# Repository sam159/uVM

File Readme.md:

# uVM

This is an 8-bit virtual machine with 16-bit addressing. It is RISC-style with no direct operations on memory, instead
operations are done on one of 16 8-bit registers with 6 16-bit registers mapped over them.

An [ASM language](ASM.md) is defined and implemented for this VM.

## Building / Running

CMake and a C build toolchain are required to build. On a debian-based system install `build-essential` and `cmake` packages.

```shell
# setup makefiles (run once)
$ cmake -DCMAKE_BUILD_TYPE=Release -G "Unix Makefiles" -S . -B ./cmake-build-release
# build project
$ cmake --build ./cmake-build-release --target uVM
```

Usage is printed with no options given.

```shell
$ ./cmake-build-release/uVM 
Usage:
  uVM program.bin                            # load at 0x0000
  uVM -a 0x100 file1.bin -a 0x200 file2.bin  # multiple files at absolute addresses
  uVM -p 0x100 program.bin                   # set PC to 0x100
  uVM -c file.asm [-o output.bin]            # assemble into binary format
```

Compiling and running asm files can be achieved with the following.  

```shell
$ ./cmake-build-release/uVM -c programs/basic.asm -o programs/basic.bin
Assembling 'programs/basic.asm' -> 'programs/basic.bin'
$ /cmake-build-release/uVM programs/basic.bin                         
Loaded 'programs/basic.bin' at 0x0000 (272 bytes)
VM Halted with code 0
PC: 0110  carry: 0  halted: 1 haltcode: 0000 (0)
R0: 00 (000) R4: 02 (002) R8: 00 (000) RC: 00 (000) 
R1: 01 (001) R5: 00 (000) R9: 00 (000) RD: 00 (000) 
R2: 64 (100) R6: 00 (000) RA: 00 (000) RE: 00 (000) 
R3: 00 (000) R7: 00 (000) RB: 00 (000) RF: 00 (000) 
RXA: 200 (00512) RXB: 00 (00000) RXE: 00 (00000)
RXC: 00 (00000) RXF: 00 (00000) RXD: 00 (00000)
```

## VM

### Registers and Flags

- **8-bit registers** 16 registers (`R0`–`RF`), 8-bit each.
- **16-bit registers** 16 registers (`RX0`-`RXF`) mapped over the 8-bit registers.
  - `RX0`-`RX9` mirroring `R0`-`RF` extended to 16-bits
  - `RXA`-`RXF` mapped to pairs of 8-bit registers
- **R0/RX0** always reads as 0. Writes to R0 are a no-op.
- **PC** (program counter), 16-bit. Increments by 2 each instruction fetch. Must be word-aligned.
- **carry**, 1-bit flag used by ADC and SBC.

### 16-bit Register Mapping

Some instructions can use two 8-bit registers as one 16-bit register for addressing. 

The upper 12 registers form six extended 16-bit address registers (big-endian, high byte : low byte):

| Alias | Registers |
|-------|-----------|
| RXA   | R4 : R5   |
| RXB   | R6 : R7   |
| RXC   | R8 : R9   |
| RXD   | RA : RB   |
| RXE   | RC : RD   |
| RXF   | RE : RF   |

`vm_get_rx()` returns the 16-bit value of a register: 0x0-0x9 return the 8-bit variant, with 0xA-0xF returning the above registers.  

### Memory

- 64KB address space (0x0000 - 0xFFFF).
- All operations work on registers only, no direct memory-to-memory operations.
- Memory access is via hook functions: `readAddr` and `writeAddr` on the VM struct.

### Instruction Format

All instructions are two bytes (big-endian). The upper four bits are the opcode. Three operand formats share the lower 12 bits:

| Format | Layout (16 bits)             | Description                                     |
|--------|------------------------------|-------------------------------------------------|
| Q      | `[op:4][rd:4][imm8:8]`       | Destination register + 8-bit immediate          |
| S      | `[op:4][rd:4][rx:4][ry:4]`   | Destination + two source registers              |
| T      | `[op:4][rd:4][rx:4][imm4:4]` | Destination + source register + 4-bit immediate |
| V      | `[op:4][imm12:12]`           | 12-bit immediate                                |

## Operations / Opcodes

Operand terms
- `exitcode` - sets the vm exitcode
- `rd`/`rx`/`ry` - 8-bit register
- `rdx` - `rd` with extended register support
- `imm4` - immediate value 4-bit
- `imm4_s` - immediate value 4-bit
- `imm4_s_x2` - immediate value 4-bit multiplied by two
- `test` - a conditional jump type
- `imm8` - immediate value 8-bit 
- `imm8_s` - signed immediate value 8-bit 
- `imm8_s_x2` - signed immediate value 8-bit multiplied by two
- `imm12` - immediate value 12-bit
- `imm12_s` - signed immediate value 12-bit
- `imm12_s_x2` - signed immediate value 12-bit multiplied by two
- `carry` - carry flag

All jumps are in words/instructions. 

| Op  | Mnemonic | Format | Operation                          | Description                                                                               |
|-----|----------|--------|------------------------------------|-------------------------------------------------------------------------------------------------|
| `0` | HLT      | Q      | `exitcode ← rd + imm8`                 | Halt the VM. Sets `halted = true`, and the exit code to `rd` + `imm8`                           |
| `1` | LDA      | T      | `rd ← [rdx + imm4]`                | Load byte from memory at 16-bit address `rdx + imm4` into `rd`                            |
| `2` | STA      | T      | `[rdx + imm4] ← rx`                | Store `rx` to memory at 16-bit address `rdx + imm4`                                       |
| `3` | LDI      | Q      | `rd ← imm8`                        | Load `imm8` into `rd`                                                                     |
| `4` | ADD      | S      | `rd ← rx + ry`                     | 8-bit add. Sets carry on overflow                                                                   |
| `5` | ADC      | S      | `rd ← rx + ry + carry`             | 8-bit add with carry. Sets carry on overflow                                              |
| `6` | SUB      | S      | `rd ← rx - ry`                     | 8-bit subtract. Clears carry                                                              |
| `7` | SBC      | S      | `rd ← rx - ry - carry`             | 8-bit subtract with borrow. Propagates borrow bit-by-bit into carry                       |
| `8` | NOT      | T      | `rd ← ~rx`                         | Bitwise NOT of `rx`                                                                       |
| `9` | BIT      | T      | `rd ← rd OP rx`                    | Bitwise operation on `rd` using `rx`. OP: 0=AND, 1=OR, 2=XOR, 4=MOD                       |
| `A` | SHL      | T      | `rd ← rx << imm4`                  | Logical left shift by `imm` bits                                                          |
| `B` | SHR      | T      | `rd ← rx >> imm4`                  | Logical right shift by `imm` bits                                                         |
| `C` | JMP      | V      | `PC ← PC + imm12_s_x2`             | Relative jump. Update PC with `imm12_s_x2`                                                |
| `D` | JPF      | Q      | `PC ← rdx + imm8_s_x2`             | Far jump. Set PC to the value in `rdx` with `imm8_s_x2` value                             |
| `E` | JNZ      | Q      | `PC ← PC + imm8_s_x2` if `rd != 0` | Conditional jump. Add `imm8_s_x2` to PC if `rd` is not zero                               |
| `F` | JPC      | T      | `PC ← PC + 2` if `!test(rd,rx)`    | Conditional jump. Skips the next instruction if `test` passes for values in `rd` and `rx` |

### Conditional Jumps

Test types, used for comparing values in `rd` and `rx`.

Tests are mapped into a 4-bit value and can be in any combination
```text
3   2   1   0
|   |   |   |
|   |   |   +-- Equality
|   |   +------ Less Than
|   +---------- Greater Than
+-------------- Negate Result
```

Setting bits 0–3 will pass for any value, negating it will not pass for any value,
similarly not setting any bits will not pass for any value.

| Mnemonic | Number | Binary | Test                                         |
|----------|--------|--------|----------------------------------------------|
| EQ       | 1      | 0001   | Equals                                       |
| ~EQ      | 9      | 1001   | Not equals                                   |
| LT       | 2      | 0010   | Less than                                    |
| ~LT      | 10     | 1010   | Not less than                                |
| LTE      | 3      | 0011   | Less than or equal                           |
| ~LTE     | 11     | 1011   | Not less than or equal                       |
| GT       | 4      | 0100   | Greater than                                 |
| ~GT      | 12     | 1100   | Not greater than                             |
| GTE      | 5      | 0101   | Greater than or equal                        |
| ~GTE     | 13     | 1101   | Not greater than or equal                    |

## Error Handling

Errors are reported via the `error` hook and halt the VM:

| Code | Constant               | Condition                                                           |
|------|------------------------|---------------------------------------------------------------------|
| 1    | `VM_ERR_MISALIGN`      | PC is not word-aligned on instruction fetch.                        |
| 2    | `VM_ERR_UNKNOWN_OP`    | Opcode is not recognized (0–F). Redundant, exists for completeness. |
| 3    | `VM_ERR_OUT_OF_BOUNDS` | Memory access address >= 0x10000.                                   |
| 4    | `VM_ERR_JUMP_SELF`     | An jump instruction jumped to itself                                |
| 5    | `VM_ERR_INVALID_BIT_OP`| BIT instruction has invalid operation code (not 0, 1, 2, or 4).     |

## Execution Model

1. `vm_step()` fetches one 2-byte instruction from `readAddr(PC)`.
2. Decodes the opcode and operand format.
3. Executes the operation, writing the result to `rd` via `vm_put_r()`.
4. Increments PC by 2 (except for jumps which set PC directly).
5. The main loop calls `vm_step()` repeatedly until `vm->halted` is true.

## TODO

ASM
- allow variables in STA/LDA address offset
- allow referencing variable high/low byte with `:h`/`:l`

VM
- Add device support
  - File

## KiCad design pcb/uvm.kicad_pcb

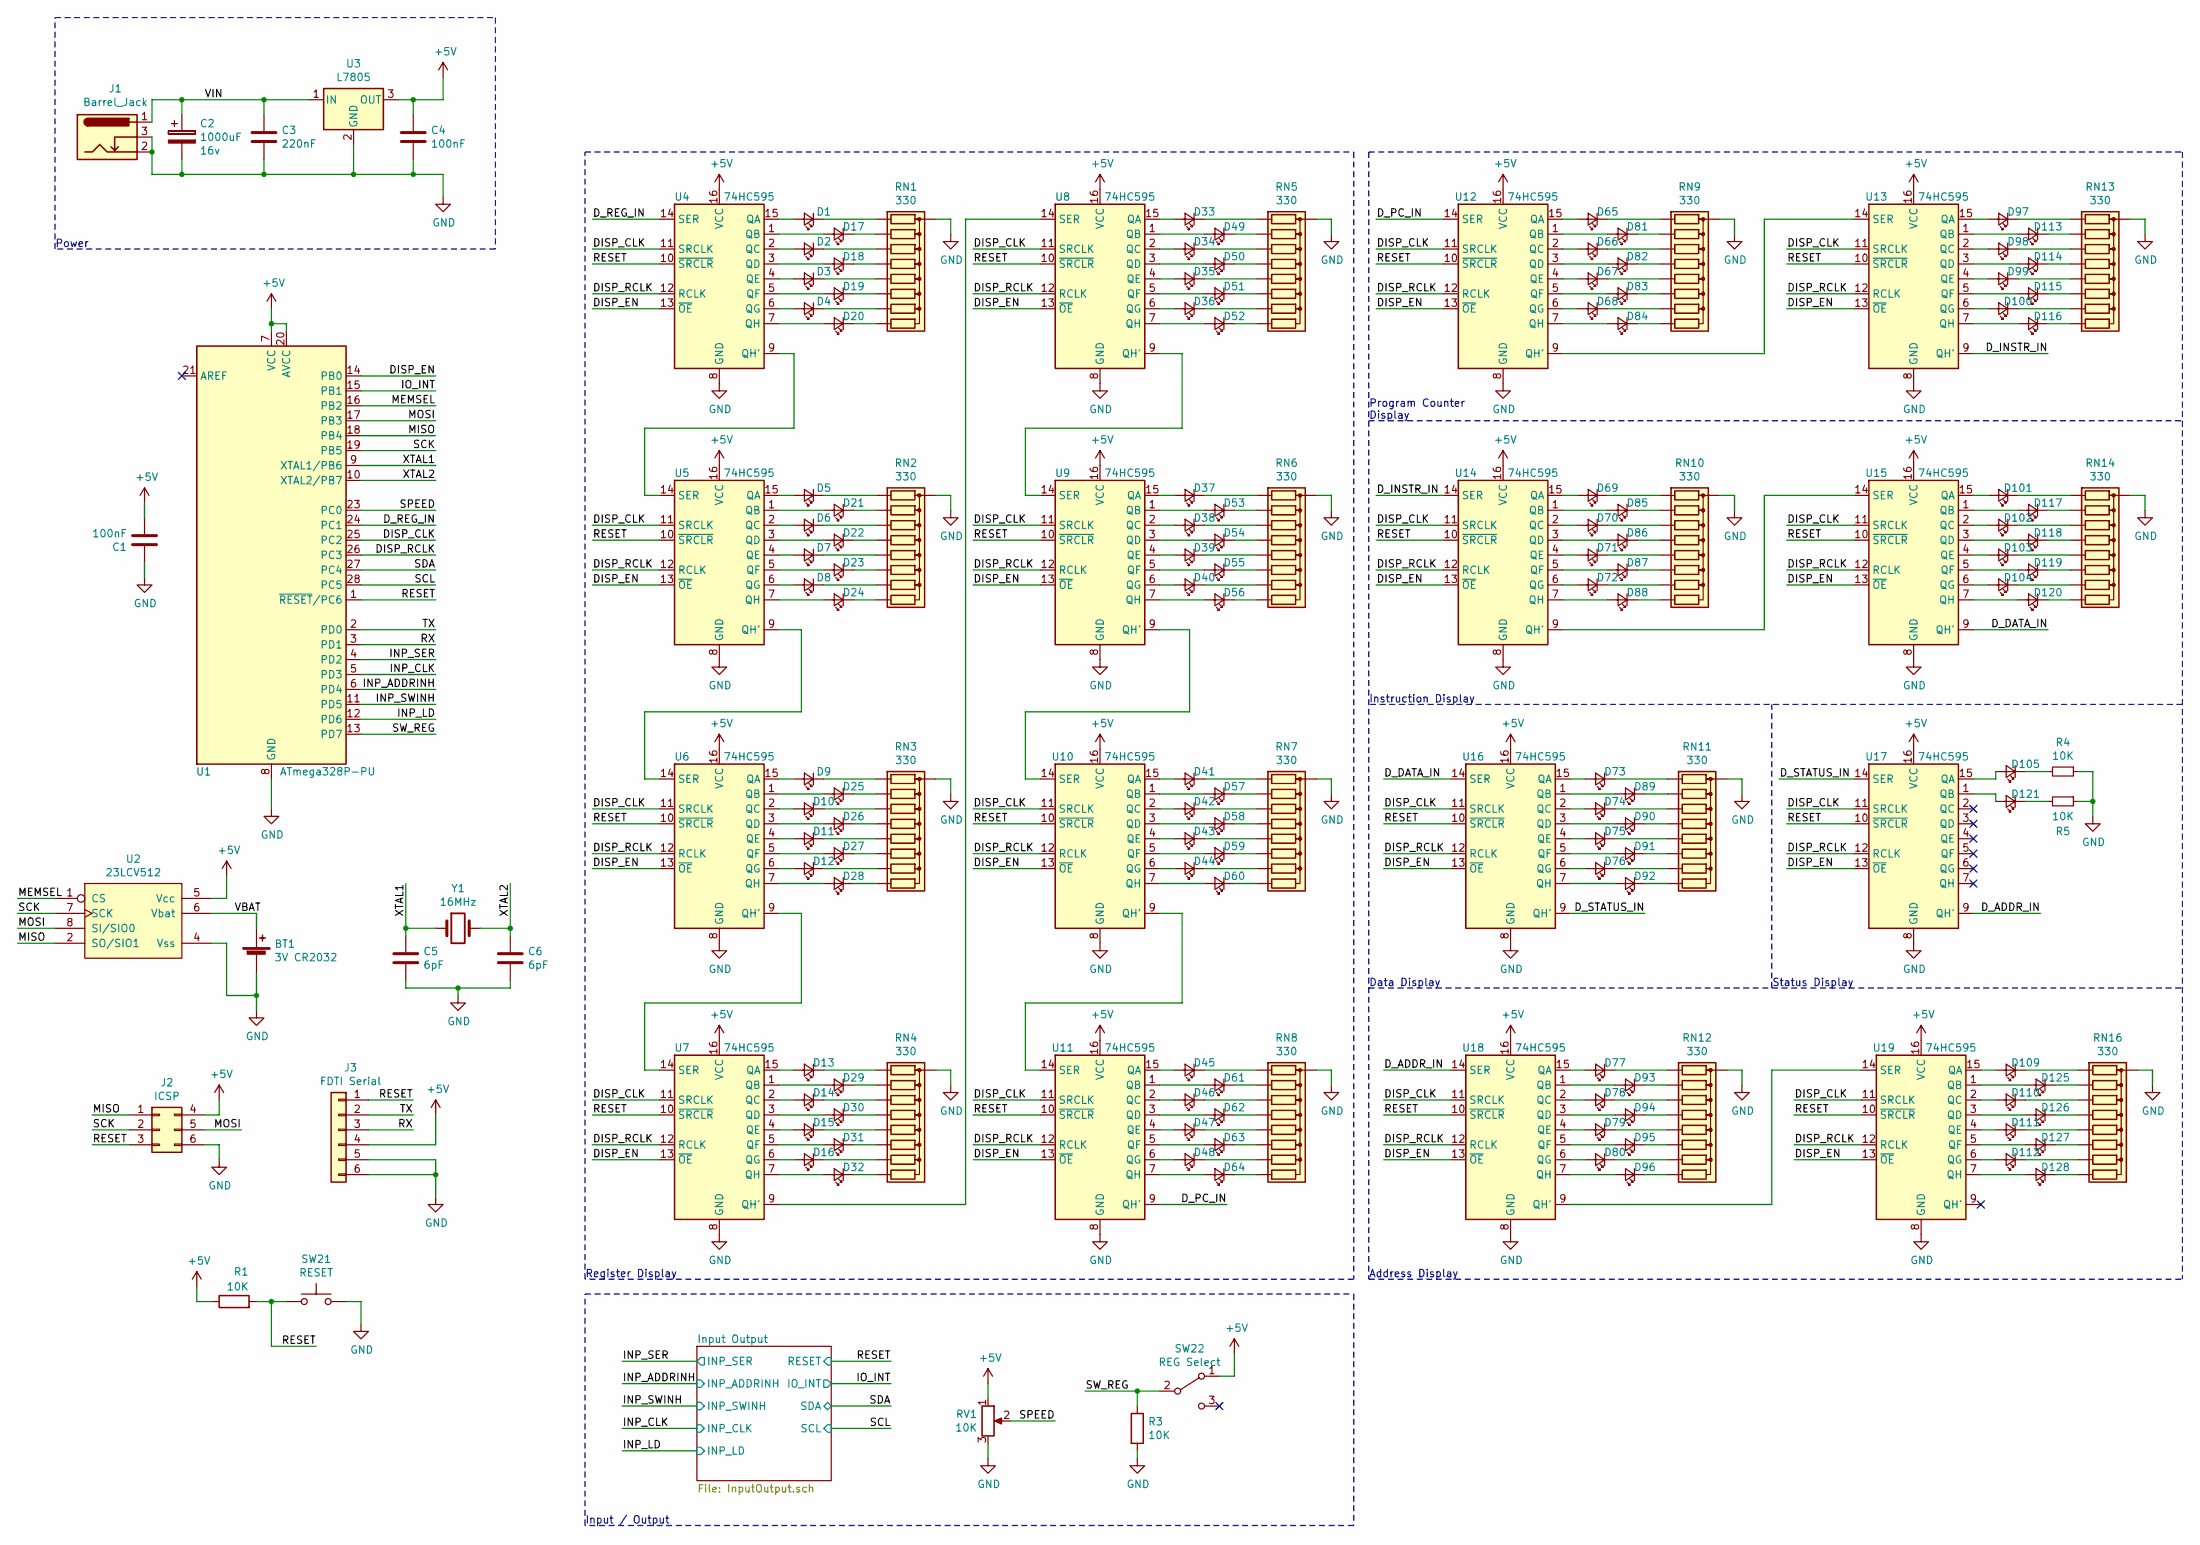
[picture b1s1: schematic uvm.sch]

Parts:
BT1: 3V CR2032; BatteryHolder_Keystone_105_1x2430
C1, C4: 100nF; C_Disc_D6.0mm_W2.5mm_P5.00mm
C2: 1000uF; CP_Radial_D8.0mm_P3.80mm; Rating 16v
C3: 220nF; C_Disc_D4.7mm_W2.5mm_P5.00mm
C5, C6: 6pF; C_Disc_D6.0mm_W2.5mm_P5.00mm
D1, D2, D3, D4, D5, D6, D7, D8, D9, D10, D11, D12, D13, D14, D15, D16, D17, D18, D19, D20, D21, D22, D23, D24, D25, D26, D27, D28, D29, D30, D31, D32, D33, D34, D35, D36, D37, D38, D39, D40, D41, D42, D43, D44, D45, D46, D47, D48, D49, D50, D51, D52, D53, D54, D55, D56, D57, D58, D59, D60, D61, D62, D63, D64, D65, D66, D67, D68, D69, D70, D71, D72, D73, D74, D75, D76, D77, D78, D79, D80, D81, D82, D83, D84, D85, D86, D87, D88, D89, D90, D91, D92, D93, D94, D95, D96, D97, D98, D99, D100, D101, D102, D103, D104, D105, D109, D110, D111, D112, D113, D114, D115, D116, D117, D118, D119, D120, D121, D125, D126, D127, D128: LED; LED_D5.0mm
J1: Barrel_Jack; BarrelJack_Horizontal
J2: ICSP; PinHeader_2x03_P2.54mm_Vertical
J3: FDTI Serial; PinHeader_1x06_P2.54mm_Vertical
R1, R3, R4, R5: 10K; R_Axial_DIN0207_L6.3mm_D2.5mm_P10.16mm_Horizontal
RN1, RN2, RN3, RN4, RN5, RN6, RN7, RN8, RN9, RN10, RN11, RN12, RN13, RN14, RN16: 330; R_Array_SIP9
RV1: 10K; Potentiometer_Alps_RK09K_Single_Vertical
SW21: RESET; SW_PUSH_6mm_H5mm
SW22: REG Select; TOGGLE_SPDT_ON_ON_2MS
U1: ATmega328P-PU; DIP-28_W7.62mm_Socket
U2: 23LCV512; DIP-8_W7.62mm_Socket
U3: L7805; TO-220-3_Horizontal_TabDown
U4, U5, U6, U7, U8, U9, U10, U11, U12, U13, U14, U15, U16, U17, U18, U19: 74HC595; DIP-16_W7.62mm
Y1: 16MHz; Crystal_HC18-U_Vertical

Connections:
+5V: C1.2, C4.1, J2.4, J3.4, R1.1, RV1.1, SW22.1 (A), U1.7 (VCC), U1.20 (AVCC), U2.5 (Vcc), U3.3 (OUT), U4.16 (VCC), U5.16 (VCC), U6.16 (VCC), U7.16 (VCC), U8.16 (VCC), U9.16 (VCC), U10.16 (VCC), U11.16 (VCC), U12.16 (VCC), U13.16 (VCC), U14.16 (VCC), U15.16 (VCC), U16.16 (VCC), U17.16 (VCC), U18.16 (VCC), U19.16 (VCC); also elsewhere on the board
/DISP_CLK: U1.25 (PC2), U4.11 (SRCLK), U5.11 (SRCLK), U6.11 (SRCLK), U7.11 (SRCLK), U8.11 (SRCLK), U9.11 (SRCLK), U10.11 (SRCLK), U11.11 (SRCLK), U12.11 (SRCLK), U13.11 (SRCLK), U14.11 (SRCLK), U15.11 (SRCLK), U16.11 (SRCLK), U17.11 (SRCLK), U18.11 (SRCLK), U19.11 (SRCLK)
/DISP_EN: U1.14 (PB0), U4.13 (~OE), U5.13 (~OE), U6.13 (~OE), U7.13 (~OE), U8.13 (~OE), U9.13 (~OE), U10.13 (~OE), U11.13 (~OE), U12.13 (~OE), U13.13 (~OE), U14.13 (~OE), U15.13 (~OE), U16.13 (~OE), U17.13 (~OE), U18.13 (~OE), U19.13 (~OE)
/DISP_RCLK: U1.26 (PC3), U4.12 (RCLK), U5.12 (RCLK), U6.12 (RCLK), U7.12 (RCLK), U8.12 (RCLK), U9.12 (RCLK), U10.12 (RCLK), U11.12 (RCLK), U12.12 (RCLK), U13.12 (RCLK), U14.12 (RCLK), U15.12 (RCLK), U16.12 (RCLK), U17.12 (RCLK), U18.12 (RCLK), U19.12 (RCLK)
/D_ADDR_IN: U17.9 (QH'), U18.14 (SER)
/D_DATA_IN: U15.9 (QH'), U16.14 (SER)
/D_INSTR_IN: U13.9 (QH'), U14.14 (SER)
/D_PC_IN: U11.9 (QH'), U12.14 (SER)
/D_REG_IN: U1.24 (PC1), U4.14 (SER)
/D_STATUS_IN: U16.9 (QH'), U17.14 (SER)
/INP_ADDRINH: U1.6 (PD4); also elsewhere on the board
/INP_CLK: U1.5 (PD3); also elsewhere on the board
/INP_LD: U1.12 (PD6); also elsewhere on the board
/INP_SER: U1.4 (PD2); also elsewhere on the board
/INP_SWINH: U1.11 (PD5); also elsewhere on the board
/IO_INT: U1.15 (PB1); also elsewhere on the board
/MEMSEL: U1.16 (PB2), U2.1 (CS)
/MISO: J2.1, U1.18 (PB4), U2.2 (SO/SIO1)
/MOSI: J2.5, U1.17 (PB3), U2.8 (SI/SIO0)
/RESET: J2.3, J3.1, R1.2, SW21.1, U1.1 (~RESET~/PC6), U4.10 (~SRCLR), U5.10 (~SRCLR), U6.10 (~SRCLR), U7.10 (~SRCLR), U8.10 (~SRCLR), U9.10 (~SRCLR), U10.10 (~SRCLR), U11.10 (~SRCLR), U12.10 (~SRCLR), U13.10 (~SRCLR), U14.10 (~SRCLR), U15.10 (~SRCLR), U16.10 (~SRCLR), U17.10 (~SRCLR), U18.10 (~SRCLR), U19.10 (~SRCLR); also elsewhere on the board
/RX: J3.3, U1.3 (PD1)
/SCK: J2.2, U1.19 (PB5), U2.7 (SCK)
/SCL: U1.28 (PC5); also elsewhere on the board
/SDA: U1.27 (PC4); also elsewhere on the board
/SPEED: RV1.2, U1.23 (PC0)
/SW_REG: R3.1, SW22.2 (B), U1.13 (PD7)
/TX: J3.2, U1.2 (PD0)
/VBAT: BT1.1 (+), U2.6 (Vbat)
/VIN: C2.1, C3.1, J1.1, U3.1 (IN)
/XTAL1: C5.1, U1.9 (XTAL1/PB6), Y1.1
/XTAL2: C6.1, U1.10 (XTAL2/PB7), Y1.2
GND: BT1.2 (-), C1.1, C2.2, C3.2, C4.2, C5.2, C6.2, J1.2, J1.3, J2.6, J3.5, J3.6, R3.2, R4.1, R5.1, RN1.1 (common), RN2.1 (common), RN3.1 (common), RN4.1 (common), RN5.1 (common), RN6.1 (common), RN7.1 (common), RN8.1 (common), RN9.1 (common), RN10.1 (common), RN11.1 (common), RN12.1 (common), RN13.1 (common), RN14.1 (common), RN16.1 (common), RV1.3, SW21.2, U1.8 (GND), U1.22 (GND), U2.4 (Vss), U3.2 (GND), U4.8 (GND), U5.8 (GND), U6.8 (GND), U7.8 (GND), U8.8 (GND), U9.8 (GND), U10.8 (GND), U11.8 (GND), U12.8 (GND), U13.8 (GND), U14.8 (GND), U15.8 (GND), U16.8 (GND), U17.8 (GND), U18.8 (GND), U19.8 (GND); also elsewhere on the board
unnamed: D1.1 (K), RN1.2 (R1)
unnamed: D1.2 (A), U4.15 (QA)
unnamed: D2.1 (K), RN1.4 (R3)
unnamed: D2.2 (A), U4.2 (QC)
unnamed: D3.1 (K), RN1.6 (R5)
unnamed: D3.2 (A), U4.4 (QE)
unnamed: D4.1 (K), RN1.8 (R7)
unnamed: D4.2 (A), U4.6 (QG)
unnamed: D5.1 (K), RN2.2 (R1)
unnamed: D5.2 (A), U5.15 (QA)
unnamed: D6.1 (K), RN2.4 (R3)
unnamed: D6.2 (A), U5.2 (QC)
unnamed: D7.1 (K), RN2.6 (R5)
unnamed: D7.2 (A), U5.4 (QE)
unnamed: D8.1 (K), RN2.8 (R7)
unnamed: D8.2 (A), U5.6 (QG)
unnamed: D9.1 (K), RN3.2 (R1)
unnamed: D9.2 (A), U6.15 (QA)
unnamed: D10.1 (K), RN3.4 (R3)
unnamed: D10.2 (A), U6.2 (QC)
unnamed: D11.1 (K), RN3.6 (R5)
unnamed: D11.2 (A), U6.4 (QE)
unnamed: D12.1 (K), RN3.8 (R7)
unnamed: D12.2 (A), U6.6 (QG)
unnamed: D13.1 (K), RN4.2 (R1)
unnamed: D13.2 (A), U7.15 (QA)
unnamed: D14.1 (K), RN4.4 (R3)
unnamed: D14.2 (A), U7.2 (QC)
unnamed: D15.1 (K), RN4.6 (R5)
unnamed: D15.2 (A), U7.4 (QE)
unnamed: D16.1 (K), RN4.8 (R7)
unnamed: D16.2 (A), U7.6 (QG)
unnamed: D17.1 (K), RN1.3 (R2)
unnamed: D17.2 (A), U4.1 (QB)
unnamed: D18.1 (K), RN1.5 (R4)
unnamed: D18.2 (A), U4.3 (QD)
unnamed: D19.1 (K), RN1.7 (R6)
unnamed: D19.2 (A), U4.5 (QF)
unnamed: D20.1 (K), RN1.9 (R8)
unnamed: D20.2 (A), U4.7 (QH)
unnamed: D21.1 (K), RN2.3 (R2)
unnamed: D21.2 (A), U5.1 (QB)
unnamed: D22.1 (K), RN2.5 (R4)
unnamed: D22.2 (A), U5.3 (QD)
unnamed: D23.1 (K), RN2.7 (R6)
unnamed: D23.2 (A), U5.5 (QF)
unnamed: D24.1 (K), RN2.9 (R8)
unnamed: D24.2 (A), U5.7 (QH)
unnamed: D25.1 (K), RN3.3 (R2)
unnamed: D25.2 (A), U6.1 (QB)
unnamed: D26.1 (K), RN3.5 (R4)
unnamed: D26.2 (A), U6.3 (QD)
unnamed: D27.1 (K), RN3.7 (R6)
unnamed: D27.2 (A), U6.5 (QF)
unnamed: D28.1 (K), RN3.9 (R8)
unnamed: D28.2 (A), U6.7 (QH)
unnamed: D29.1 (K), RN4.3 (R2)
unnamed: D29.2 (A), U7.1 (QB)
unnamed: D30.1 (K), RN4.5 (R4)
unnamed: D30.2 (A), U7.3 (QD)
unnamed: D31.1 (K), RN4.7 (R6)
unnamed: D31.2 (A), U7.5 (QF)
unnamed: D32.1 (K), RN4.9 (R8)
unnamed: D32.2 (A), U7.7 (QH)
unnamed: D33.1 (K), RN5.2 (R1)
unnamed: D33.2 (A), U8.15 (QA)
unnamed: D34.1 (K), RN5.4 (R3)
unnamed: D34.2 (A), U8.2 (QC)
unnamed: D35.1 (K), RN5.6 (R5)
unnamed: D35.2 (A), U8.4 (QE)
unnamed: D36.1 (K), RN5.8 (R7)
unnamed: D36.2 (A), U8.6 (QG)
unnamed: D37.1 (K), RN6.2 (R1)
unnamed: D37.2 (A), U9.15 (QA)
unnamed: D38.1 (K), RN6.4 (R3)
unnamed: D38.2 (A), U9.2 (QC)
unnamed: D39.1 (K), RN6.6 (R5)
unnamed: D39.2 (A), U9.4 (QE)
unnamed: D40.1 (K), RN6.8 (R7)
unnamed: D40.2 (A), U9.6 (QG)
unnamed: D41.1 (K), RN7.2 (R1)
unnamed: D41.2 (A), U10.15 (QA)
unnamed: D42.1 (K), RN7.4 (R3)
unnamed: D42.2 (A), U10.2 (QC)
unnamed: D43.1 (K), RN7.6 (R5)
unnamed: D43.2 (A), U10.4 (QE)
unnamed: D44.1 (K), RN7.8 (R7)
unnamed: D44.2 (A), U10.6 (QG)
unnamed: D45.1 (K), RN8.2 (R1)
unnamed: D45.2 (A), U11.15 (QA)
unnamed: D46.1 (K), RN8.4 (R3)
unnamed: D46.2 (A), U11.2 (QC)
unnamed: D47.1 (K), RN8.6 (R5)
unnamed: D47.2 (A), U11.4 (QE)
unnamed: D48.1 (K), RN8.8 (R7)
unnamed: D48.2 (A), U11.6 (QG)
unnamed: D49.1 (K), RN5.3 (R2)
unnamed: D49.2 (A), U8.1 (QB)
unnamed: D50.1 (K), RN5.5 (R4)
unnamed: D50.2 (A), U8.3 (QD)
unnamed: D51.1 (K), RN5.7 (R6)
unnamed: D51.2 (A), U8.5 (QF)
unnamed: D52.1 (K), RN5.9 (R8)
unnamed: D52.2 (A), U8.7 (QH)
unnamed: D53.1 (K), RN6.3 (R2)
unnamed: D53.2 (A), U9.1 (QB)
unnamed: D54.1 (K), RN6.5 (R4)
unnamed: D54.2 (A), U9.3 (QD)
unnamed: D55.1 (K), RN6.7 (R6)
unnamed: D55.2 (A), U9.5 (QF)
unnamed: D56.1 (K), RN6.9 (R8)
unnamed: D56.2 (A), U9.7 (QH)
unnamed: D57.1 (K), RN7.3 (R2)
unnamed: D57.2 (A), U10.1 (QB)
unnamed: D58.1 (K), RN7.5 (R4)
unnamed: D58.2 (A), U10.3 (QD)
unnamed: D59.1 (K), RN7.7 (R6)
unnamed: D59.2 (A), U10.5 (QF)
unnamed: D60.1 (K), RN7.9 (R8)
unnamed: D60.2 (A), U10.7 (QH)
unnamed: D61.1 (K), RN8.3 (R2)
unnamed: D61.2 (A), U11.1 (QB)
unnamed: D62.1 (K), RN8.5 (R4)
unnamed: D62.2 (A), U11.3 (QD)
unnamed: D63.1 (K), RN8.7 (R6)
unnamed: D63.2 (A), U11.5 (QF)
unnamed: D64.1 (K), RN8.9 (R8)
unnamed: D64.2 (A), U11.7 (QH)
unnamed: D65.1 (K), RN9.2 (R1)
unnamed: D65.2 (A), U12.15 (QA)
unnamed: D66.1 (K), RN9.4 (R3)
unnamed: D66.2 (A), U12.2 (QC)
unnamed: D67.1 (K), RN9.6 (R5)
unnamed: D67.2 (A), U12.4 (QE)
unnamed: D68.1 (K), RN9.8 (R7)
unnamed: D68.2 (A), U12.6 (QG)
unnamed: D69.1 (K), RN10.2 (R1)
unnamed: D69.2 (A), U14.15 (QA)
unnamed: D70.1 (K), RN10.4 (R3)
unnamed: D70.2 (A), U14.2 (QC)
unnamed: D71.1 (K), RN10.6 (R5)
unnamed: D71.2 (A), U14.4 (QE)
unnamed: D72.1 (K), RN10.8 (R7)
unnamed: D72.2 (A), U14.6 (QG)
unnamed: D73.1 (K), RN11.2 (R1)
unnamed: D73.2 (A), U16.15 (QA)
unnamed: D74.1 (K), RN11.4 (R3)
unnamed: D74.2 (A), U16.2 (QC)
unnamed: D75.1 (K), RN11.6 (R5)
unnamed: D75.2 (A), U16.4 (QE)
unnamed: D76.1 (K), RN11.8 (R7)
unnamed: D76.2 (A), U16.6 (QG)
unnamed: D77.1 (K), RN12.2 (R1)
unnamed: D77.2 (A), U18.15 (QA)
unnamed: D78.1 (K), RN12.4 (R3)
unnamed: D78.2 (A), U18.2 (QC)
unnamed: D79.1 (K), RN12.6 (R5)
unnamed: D79.2 (A), U18.4 (QE)
unnamed: D80.1 (K), RN12.8 (R7)
unnamed: D80.2 (A), U18.6 (QG)
unnamed: D81.1 (K), RN9.3 (R2)
unnamed: D81.2 (A), U12.1 (QB)
unnamed: D82.1 (K), RN9.5 (R4)
unnamed: D82.2 (A), U12.3 (QD)
unnamed: D83.1 (K), RN9.7 (R6)
unnamed: D83.2 (A), U12.5 (QF)
unnamed: D84.1 (K), RN9.9 (R8)
unnamed: D84.2 (A), U12.7 (QH)
unnamed: D85.1 (K), RN10.3 (R2)
unnamed: D85.2 (A), U14.1 (QB)
unnamed: D86.1 (K), RN10.5 (R4)
unnamed: D86.2 (A), U14.3 (QD)
unnamed: D87.1 (K), RN10.7 (R6)
unnamed: D87.2 (A), U14.5 (QF)
unnamed: D88.1 (K), RN10.9 (R8)
unnamed: D88.2 (A), U14.7 (QH)
unnamed: D89.1 (K), RN11.3 (R2)
unnamed: D89.2 (A), U16.1 (QB)
unnamed: D90.1 (K), RN11.5 (R4)
unnamed: D90.2 (A), U16.3 (QD)
unnamed: D91.1 (K), RN11.7 (R6)
unnamed: D91.2 (A), U16.5 (QF)
unnamed: D92.1 (K), RN11.9 (R8)
unnamed: D92.2 (A), U16.7 (QH)
unnamed: D93.1 (K), RN12.3 (R2)
unnamed: D93.2 (A), U18.1 (QB)
unnamed: D94.1 (K), RN12.5 (R4)
unnamed: D94.2 (A), U18.3 (QD)
unnamed: D95.1 (K), RN12.7 (R6)
unnamed: D95.2 (A), U18.5 (QF)
unnamed: D96.1 (K), RN12.9 (R8)
unnamed: D96.2 (A), U18.7 (QH)
unnamed: D97.1 (K), RN13.2 (R1)
unnamed: D97.2 (A), U13.15 (QA)
unnamed: D98.1 (K), RN13.4 (R3)
unnamed: D98.2 (A), U13.2 (QC)
unnamed: D99.1 (K), RN13.6 (R5)
unnamed: D99.2 (A), U13.4 (QE)
unnamed: D100.1 (K), RN13.8 (R7)
unnamed: D100.2 (A), U13.6 (QG)
unnamed: D101.1 (K), RN14.2 (R1)
unnamed: D101.2 (A), U15.15 (QA)
unnamed: D102.1 (K), RN14.4 (R3)
unnamed: D102.2 (A), U15.2 (QC)
unnamed: D103.1 (K), RN14.6 (R5)
unnamed: D103.2 (A), U15.4 (QE)
unnamed: D104.1 (K), RN14.8 (R7)
unnamed: D104.2 (A), U15.6 (QG)
unnamed: D105.1 (K), R4.2
unnamed: D105.2 (A), U17.15 (QA)
unnamed: D109.1 (K), RN16.2 (R1)
unnamed: D109.2 (A), U19.15 (QA)
unnamed: D110.1 (K), RN16.4 (R3)
unnamed: D110.2 (A), U19.2 (QC)
unnamed: D111.1 (K), RN16.6 (R5)
unnamed: D111.2 (A), U19.4 (QE)
unnamed: D112.1 (K), RN16.8 (R7)
unnamed: D112.2 (A), U19.6 (QG)
unnamed: D113.1 (K), RN13.3 (R2)
unnamed: D113.2 (A), U13.1 (QB)
unnamed: D114.1 (K), RN13.5 (R4)
unnamed: D114.2 (A), U13.3 (QD)
unnamed: D115.1 (K), RN13.7 (R6)
unnamed: D115.2 (A), U13.5 (QF)
unnamed: D116.1 (K), RN13.9 (R8)
unnamed: D116.2 (A), U13.7 (QH)
unnamed: D117.1 (K), RN14.3 (R2)
unnamed: D117.2 (A), U15.1 (QB)
unnamed: D118.1 (K), RN14.5 (R4)
unnamed: D118.2 (A), U15.3 (QD)
unnamed: D119.1 (K), RN14.7 (R6)
unnamed: D119.2 (A), U15.5 (QF)
unnamed: D120.1 (K), RN14.9 (R8)
unnamed: D120.2 (A), U15.7 (QH)
unnamed: D121.1 (K), R5.2
unnamed: D121.2 (A), U17.1 (QB)
unnamed: D125.1 (K), RN16.3 (R2)
unnamed: D125.2 (A), U19.1 (QB)
unnamed: D126.1 (K), RN16.5 (R4)
unnamed: D126.2 (A), U19.3 (QD)
unnamed: D127.1 (K), RN16.7 (R6)
unnamed: D127.2 (A), U19.5 (QF)
unnamed: D128.1 (K), RN16.9 (R8)
unnamed: D128.2 (A), U19.7 (QH)
unnamed: U4.9 (QH'), U5.14 (SER)
unnamed: U5.9 (QH'), U6.14 (SER)
unnamed: U6.9 (QH'), U7.14 (SER)
unnamed: U7.9 (QH'), U8.14 (SER)
unnamed: U8.9 (QH'), U9.14 (SER)
unnamed: U10.9 (QH'), U11.14 (SER)
unnamed: U9.9 (QH'), U10.14 (SER)
unnamed: U12.9 (QH'), U13.14 (SER)
unnamed: U14.9 (QH'), U15.14 (SER)
unnamed: U18.9 (QH'), U19.14 (SER)

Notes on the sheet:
Power
Register Display
Address Display
Data Display
Instruction Display
Program Counter Display
Status Display
Input / Output

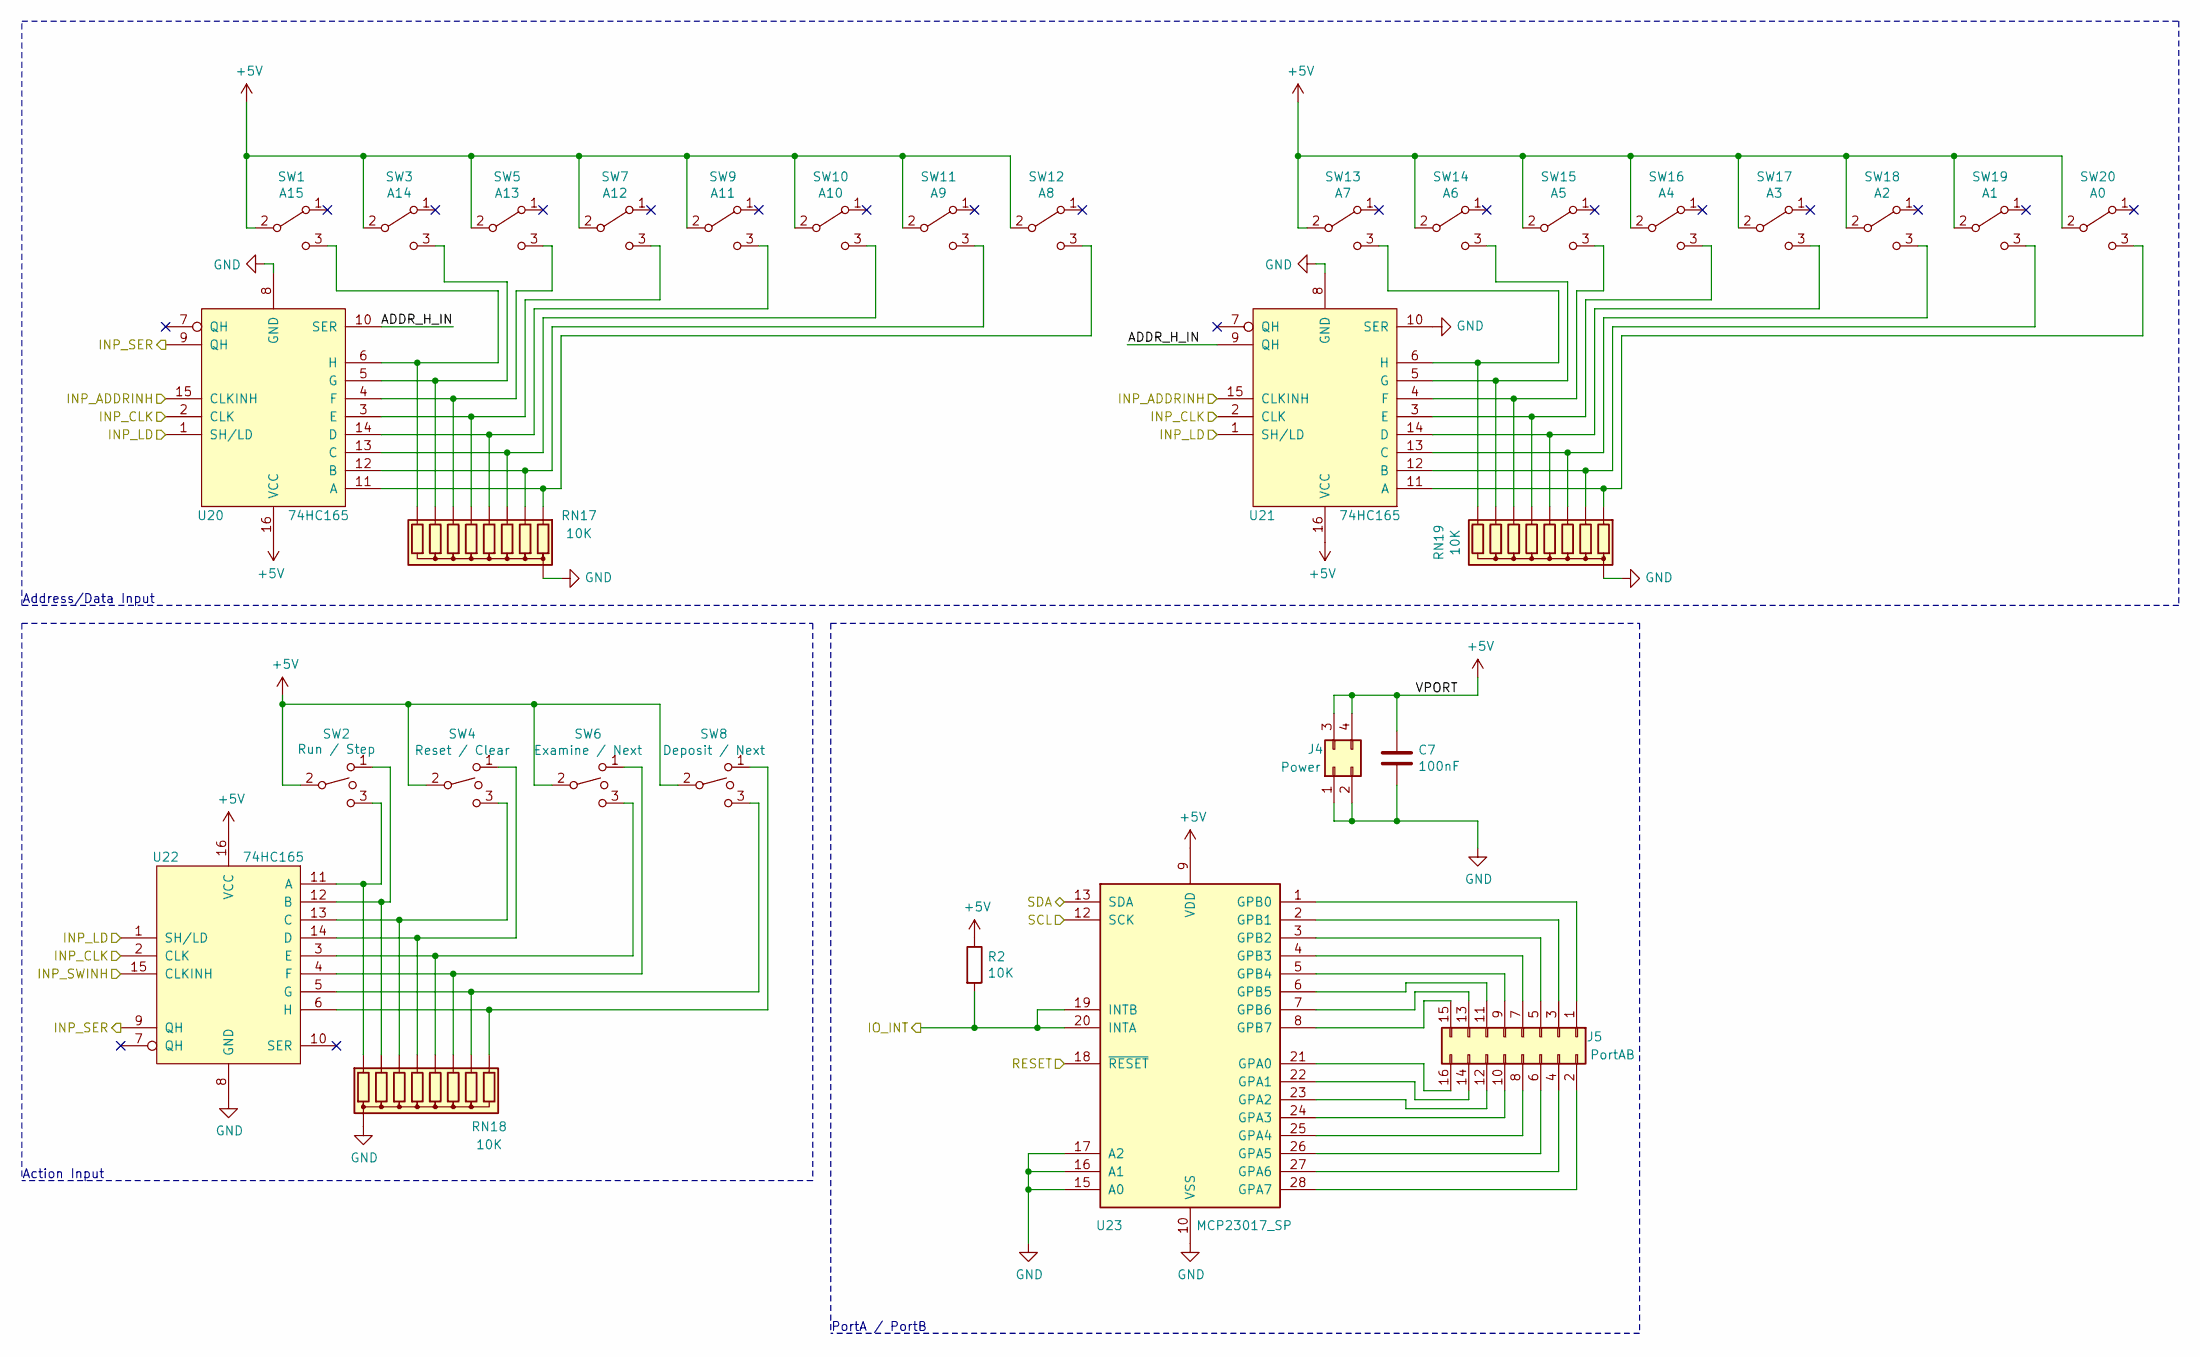
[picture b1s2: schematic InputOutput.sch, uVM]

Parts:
C7: 100nF; C_Disc_D6.0mm_W2.5mm_P5.00mm
J4: Power; PinSocket_2x02_P2.54mm_Vertical
J5: PortAB; PinSocket_2x08_P2.54mm_Vertical
R2: 10K; R_Axial_DIN0207_L6.3mm_D2.5mm_P10.16mm_Horizontal
RN17, RN18, RN19: 10K; R_Array_SIP9
SW1: A15; TOGGLE_SPDT_ON_ON_2MS
SW2: Run / Step; TOGGLE_SPDT_ON_ON_2MS
SW3: A14; TOGGLE_SPDT_ON_ON_2MS
SW4: Reset / Clear; TOGGLE_SPDT_ON_ON_2MS
SW5: A13; TOGGLE_SPDT_ON_ON_2MS
SW6: Examine / Next; TOGGLE_SPDT_ON_ON_2MS
SW7: A12; TOGGLE_SPDT_ON_ON_2MS
SW8: Deposit / Next; TOGGLE_SPDT_ON_ON_2MS
SW9: A11; TOGGLE_SPDT_ON_ON_2MS
SW10: A10; TOGGLE_SPDT_ON_ON_2MS
SW11: A9; TOGGLE_SPDT_ON_ON_2MS
SW12: A8; TOGGLE_SPDT_ON_ON_2MS
SW13: A7; TOGGLE_SPDT_ON_ON_2MS
SW14: A6; TOGGLE_SPDT_ON_ON_2MS
SW15: A5; TOGGLE_SPDT_ON_ON_2MS
SW16: A4; TOGGLE_SPDT_ON_ON_2MS
SW17: A3; TOGGLE_SPDT_ON_ON_2MS
SW18: A2; TOGGLE_SPDT_ON_ON_2MS
SW19: A1; TOGGLE_SPDT_ON_ON_2MS
SW20: A0; TOGGLE_SPDT_ON_ON_2MS
U20, U21, U22: 74HC165; DIP-16_W7.62mm
U23: MCP23017_SP; DIP-28_W7.62mm

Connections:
+5V: C7.1, J4.3, J4.4, R2.1, SW1.2 (B), SW2.2, SW3.2 (B), SW4.2, SW5.2 (B), SW6.2, SW7.2 (B), SW8.2, SW9.2 (B), SW10.2 (B), SW11.2 (B), SW12.2 (B), SW13.2 (B), SW14.2 (B), SW15.2 (B), SW16.2 (B), SW17.2 (B), SW18.2 (B), SW19.2 (B), SW20.2 (B), U20.16 (VCC), U21.16 (VCC), U22.16 (VCC), U23.9 (VDD); also elsewhere on the board
/INP_ADDRINH: U20.15 (CLKINH), U21.15 (CLKINH); also elsewhere on the board
/INP_CLK: U20.2 (CLK), U21.2 (CLK), U22.2 (CLK); also elsewhere on the board
/INP_LD: U20.1 (SH/LD), U21.1 (SH/LD), U22.1 (SH/LD); also elsewhere on the board
/INP_SER: U20.9 (QH), U22.9 (QH); also elsewhere on the board
/INP_SWINH: U22.15 (CLKINH); also elsewhere on the board
/IO_INT: R2.2, U23.19 (INTB), U23.20 (INTA); also elsewhere on the board
/Input Output/ADDR_H_IN: U20.10 (SER), U21.9 (QH)
/RESET: U23.18 (~RESET~); also elsewhere on the board
/SCL: U23.12 (SCK); also elsewhere on the board
/SDA: U23.13 (SDA); also elsewhere on the board
GND: C7.2, J4.1, J4.2, RN17.1 (common), RN18.1 (common), RN19.1 (common), U20.8 (GND), U21.8 (GND), U21.10 (SER), U22.8 (GND), U23.10 (VSS), U23.15 (A0), U23.16 (A1), U23.17 (A2); also elsewhere on the board
unnamed: J5.1, U23.1 (GPB0)
unnamed: J5.2, U23.28 (GPA7)
unnamed: J5.3, U23.2 (GPB1)
unnamed: J5.4, U23.27 (GPA6)
unnamed: J5.5, U23.3 (GPB2)
unnamed: J5.6, U23.26 (GPA5)
unnamed: J5.7, U23.4 (GPB3)
unnamed: J5.8, U23.25 (GPA4)
unnamed: J5.9, U23.5 (GPB4)
unnamed: J5.10, U23.24 (GPA3)
unnamed: J5.11, U23.6 (GPB5)
unnamed: J5.12, U23.23 (GPA2)
unnamed: J5.13, U23.7 (GPB6)
unnamed: J5.14, U23.22 (GPA1)
unnamed: J5.15, U23.8 (GPB7)
unnamed: J5.16, U23.21 (GPA0)
unnamed: RN17.2 (R1), SW12.3 (C), U20.11 (A)
unnamed: RN17.3 (R2), SW11.3 (C), U20.12 (B)
unnamed: RN17.4 (R3), SW10.3 (C), U20.13 (C)
unnamed: RN17.5 (R4), SW9.3 (C), U20.14 (D)
unnamed: RN17.6 (R5), SW7.3 (C), U20.3 (E)
unnamed: RN17.7 (R6), SW5.3 (C), U20.4 (F)
unnamed: RN17.8 (R7), SW3.3 (C), U20.5 (G)
unnamed: RN17.9 (R8), SW1.3 (C), U20.6 (H)
unnamed: RN18.2 (R1), SW2.3, U22.11 (A)
unnamed: RN18.3 (R2), SW2.1, U22.12 (B)
unnamed: RN18.4 (R3), SW4.3, U22.13 (C)
unnamed: RN18.5 (R4), SW4.1, U22.14 (D)
unnamed: RN18.6 (R5), SW6.3, U22.3 (E)
unnamed: RN18.7 (R6), SW6.1, U22.4 (F)
unnamed: RN18.8 (R7), SW8.3, U22.5 (G)
unnamed: RN18.9 (R8), SW8.1, U22.6 (H)
unnamed: RN19.2 (R1), SW20.3 (C), U21.11 (A)
unnamed: RN19.3 (R2), SW19.3 (C), U21.12 (B)
unnamed: RN19.4 (R3), SW18.3 (C), U21.13 (C)
unnamed: RN19.5 (R4), SW17.3 (C), U21.14 (D)
unnamed: RN19.6 (R5), SW16.3 (C), U21.3 (E)
unnamed: RN19.7 (R6), SW15.3 (C), U21.4 (F)
unnamed: RN19.8 (R7), SW14.3 (C), U21.5 (G)
unnamed: RN19.9 (R8), SW13.3 (C), U21.6 (H)

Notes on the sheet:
Address/Data Input
Action Input
PortA / PortB

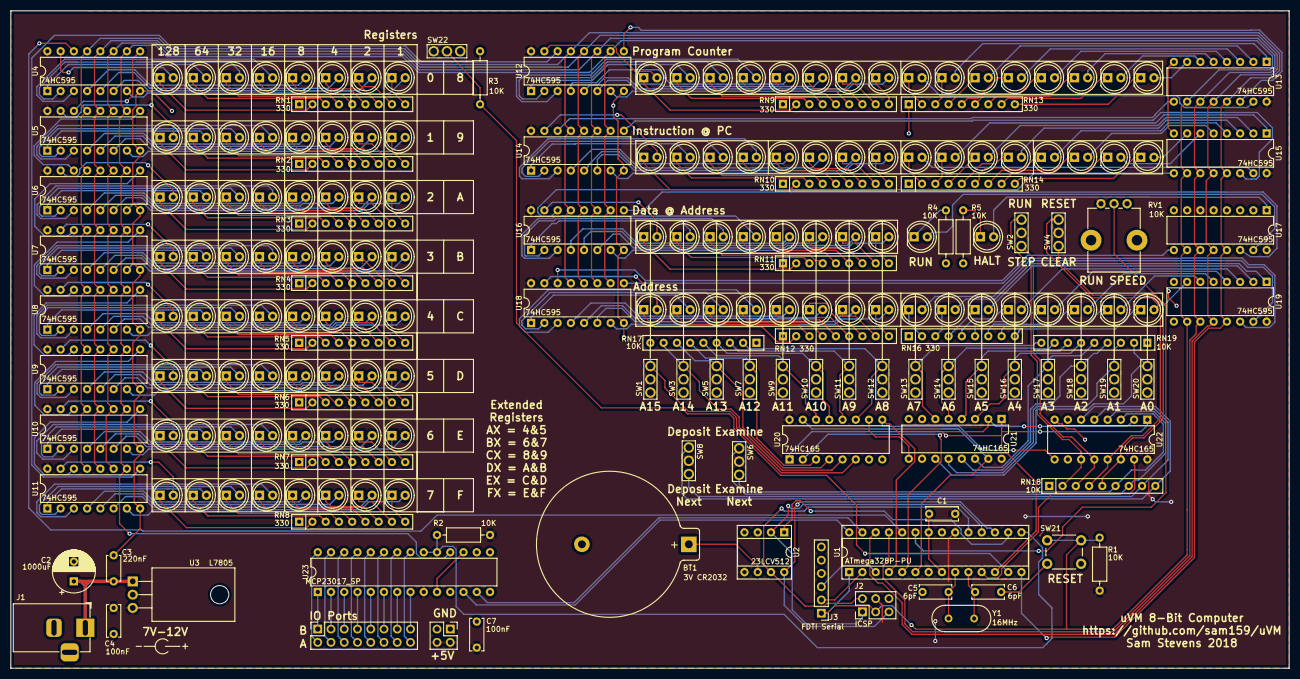
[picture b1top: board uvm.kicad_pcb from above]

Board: 2 copper layers, 245.0 x 126.0 mm, 205 parts (0 on the bottom side), 327 nets.

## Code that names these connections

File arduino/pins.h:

/*
Copyright 2018 Sam Stevens

Licensed under the Apache License, Version 2.0 (the "License");
you may not use this file except in compliance with the License.
You may obtain a copy of the License at

   http://www.apache.org/licenses/LICENSE-2.0

Unless required by applicable law or agreed to in writing, software
distributed under the License is distributed on an "AS IS" BASIS,
WITHOUT WARRANTIES OR CONDITIONS OF ANY KIND, either express or implied.
See the License for the specific language governing permissions and
limitations under the License.
 */

#ifndef UVM_PINS_H
#define UVM_PINS_H

//Display / Shift register output
#define PIN_DISP_EN   8
#define PIN_DISP_CLK  16
#define PIN_DISP_RCLK 17
#define PIN_DISP_OUT  15

//Inputs
#define PIN_SPEED        14
#define PIN_SW_REG       7
#define PIN_INP_SER      2
#define PIN_INP_CLK      3
#define PIN_INP_ADDR_INH 4
#define PIN_INP_SW_INH   5
#define PIN_INP_LOAD     6

//I/O
#define PIN_IO_INT 9

//Memory
#define PIN_MEMORY_SEL 10

#endif

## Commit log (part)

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2018-10-16 Initial Commit`
2018-10-16 Removed temp var. Fixed PC.
    Changed PC to be 8bits and checking for alignment.
    Introduced x/y vars.
2018-10-16 Added Apache 2.0 License.
2018-10-21 Started on arduino version
2018-10-21 Implemented basic arduino vm.
    Updated LDA to be M[D] = RX + IMM
    Updated STA to be RD = M[RX + IMM]
    Updated SYS to be RD = SYSCALL(RX, IMM)
    Added error callback to VM, replaced printfs with callback.
    Added syscalls.
2018-10-24 Implemented vm memory using external 23LCV512 chip.
    Todo: implement extended registers
2018-10-26 Added TTL based LRU memory cache.
2018-10-27 Implemented button input using 74HC165 shift registers.
2018-10-28 Updated filenames
2018-10-28 Implemented extended registers AX-FX.
2018-10-29 Added PCB Schematic for uVM.
2018-10-30 Completed Schematic and assigned footprints.
    Started PCB layout.
2018-10-31 Working on PCB layout.
2018-11-01 Completed PCB Layout.
2018-11-11 Implemented base system for REV.A PCB.
2018-11-11 Added notes for PCB Rev.A
2018-11-11 Fixed typos in pcb history
2018-11-12 Changed ADD to clear and populate carry.
    Run/Step only when not halted.
    Reversed speed control.
2026-06-27 updated vm.c to reflect the arduino one
2026-06-28 updated readme and entrypoint to allow running binaries
2026-06-28 started on ASM compiler
2026-06-28 updated agents
2026-06-28 reworked instruction set
2026-06-28 working on asm
2026-06-29 refined asm format
2026-06-29 refining/clarifying asm format
2026-06-29 added asm tokeniser
2026-06-30 Update ASMToken lines to be variable length
    Enforced line length limit of 1024 per spec.
2026-06-30 added syntax tree, improved tokenisation
2026-06-30 fixing memory leaks
2026-06-30 simplified token appends
2026-06-30 header tidy up
    update agents
2026-06-30 added some example programs
2026-06-30 chore: add .worktrees to gitignore
2026-06-30 feat: extend asm_free_program to handle all union members
2026-06-30 feat: append EOF token before calling asm_parse
2026-06-30 fix: use strdup for EOF token value to avoid freeing string literal
2026-06-30 feat: implement main parse loop with empty line handling
2026-06-30 feat: implement :origin directive parsing
2026-06-30 feat: implement alias directive parsing
2026-06-30 feat: implement :data directive parsing (DB, DW, STZ, STL)
2026-06-30 feat: add operand parsing helpers for registers
2026-06-30 feat: implement basic instruction parsing (no operands yet)
2026-06-30 fix: swap JMP/JPF opcode mappings in assembler
2026-06-30 test: add integration test for example programs
2026-06-30 store label on ASMProgramData instead of discarding it
2026-06-30 rename enum values to match opcode names: JMP/JPF/JNZ/JPC
2026-06-30 docs: add implementation status and next steps notes
